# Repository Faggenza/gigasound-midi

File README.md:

# Gigasound MIDI Polyphonic Keyboard

A USB-connected MPE MIDI keyboard using piezoresistive sensors for expressive, pressure-sensitive input, built around the STM32F401 microcontroller.

## Source Tree

```
├── sprite/     # Assets in aseprite format
├── assets_src/ # Assets in bitmap format 
├── convert_asset.py # Asset convertion tool
├── emulator/
│   ├── emulator.h
│   └── Makefile
├── gigasound-hw/ # PCB KiCad files
├── include/
│   ├── adc.h
│   ├── assets.h
│   ├── bootloader.h
│   ├── calibrate.h
│   ├── config.h
│   ├── eeprom.h
│   ├── init.h
│   ├── input.h
│   ├── led.h
│   ├── main.h
│   ├── midi.h
│   ├── scale.h
│   ├── ssd1306.h
│   ├── stm32f4xx_it.h
│   ├── tusb_config.h
│   ├── uart.h
│   └── ui/
├── lib
│   └── gigagl # embedded graphics library
├── platformio.ini 
└── src/
    ├── adc.c
    ├── assets
    ├── calibrate.c
    ├── config.c
    ├── eeprom.c
    ├── init.c
    ├── input.c
    ├── led.c
    ├── main.c
    ├── midi.c
    ├── scale.c
    ├── stm32f4xx_hal_msp.c
    ├── stm32f4xx_it.c
    ├── uart.c
    ├── ui/               
    └── usb_descriptors.c
```

## References

MCU: [STM32F0401RE](https://www.st.com/resource/en/datasheet/stm32f401re.pdf)

Nucleo: [Schematic](https://www.st.com/resource/en/schematic_pack/mb1136-default-c04_schematic.pdf)

Piezoresistive sensor: [datasheet](https://cdn2.hubspot.net/hubfs/3899023/Interlinkelectronics%20November2017/Docs/Datasheet_FSR.pdf)

MIDI: [docs](https://drive.google.com/file/d/1QGjiK2QPPbii8YmES3vDEZlP63OGLiKr/view)

## Testing

[MPE Monitor](https://studiocode.dev/mpe-monitor/)

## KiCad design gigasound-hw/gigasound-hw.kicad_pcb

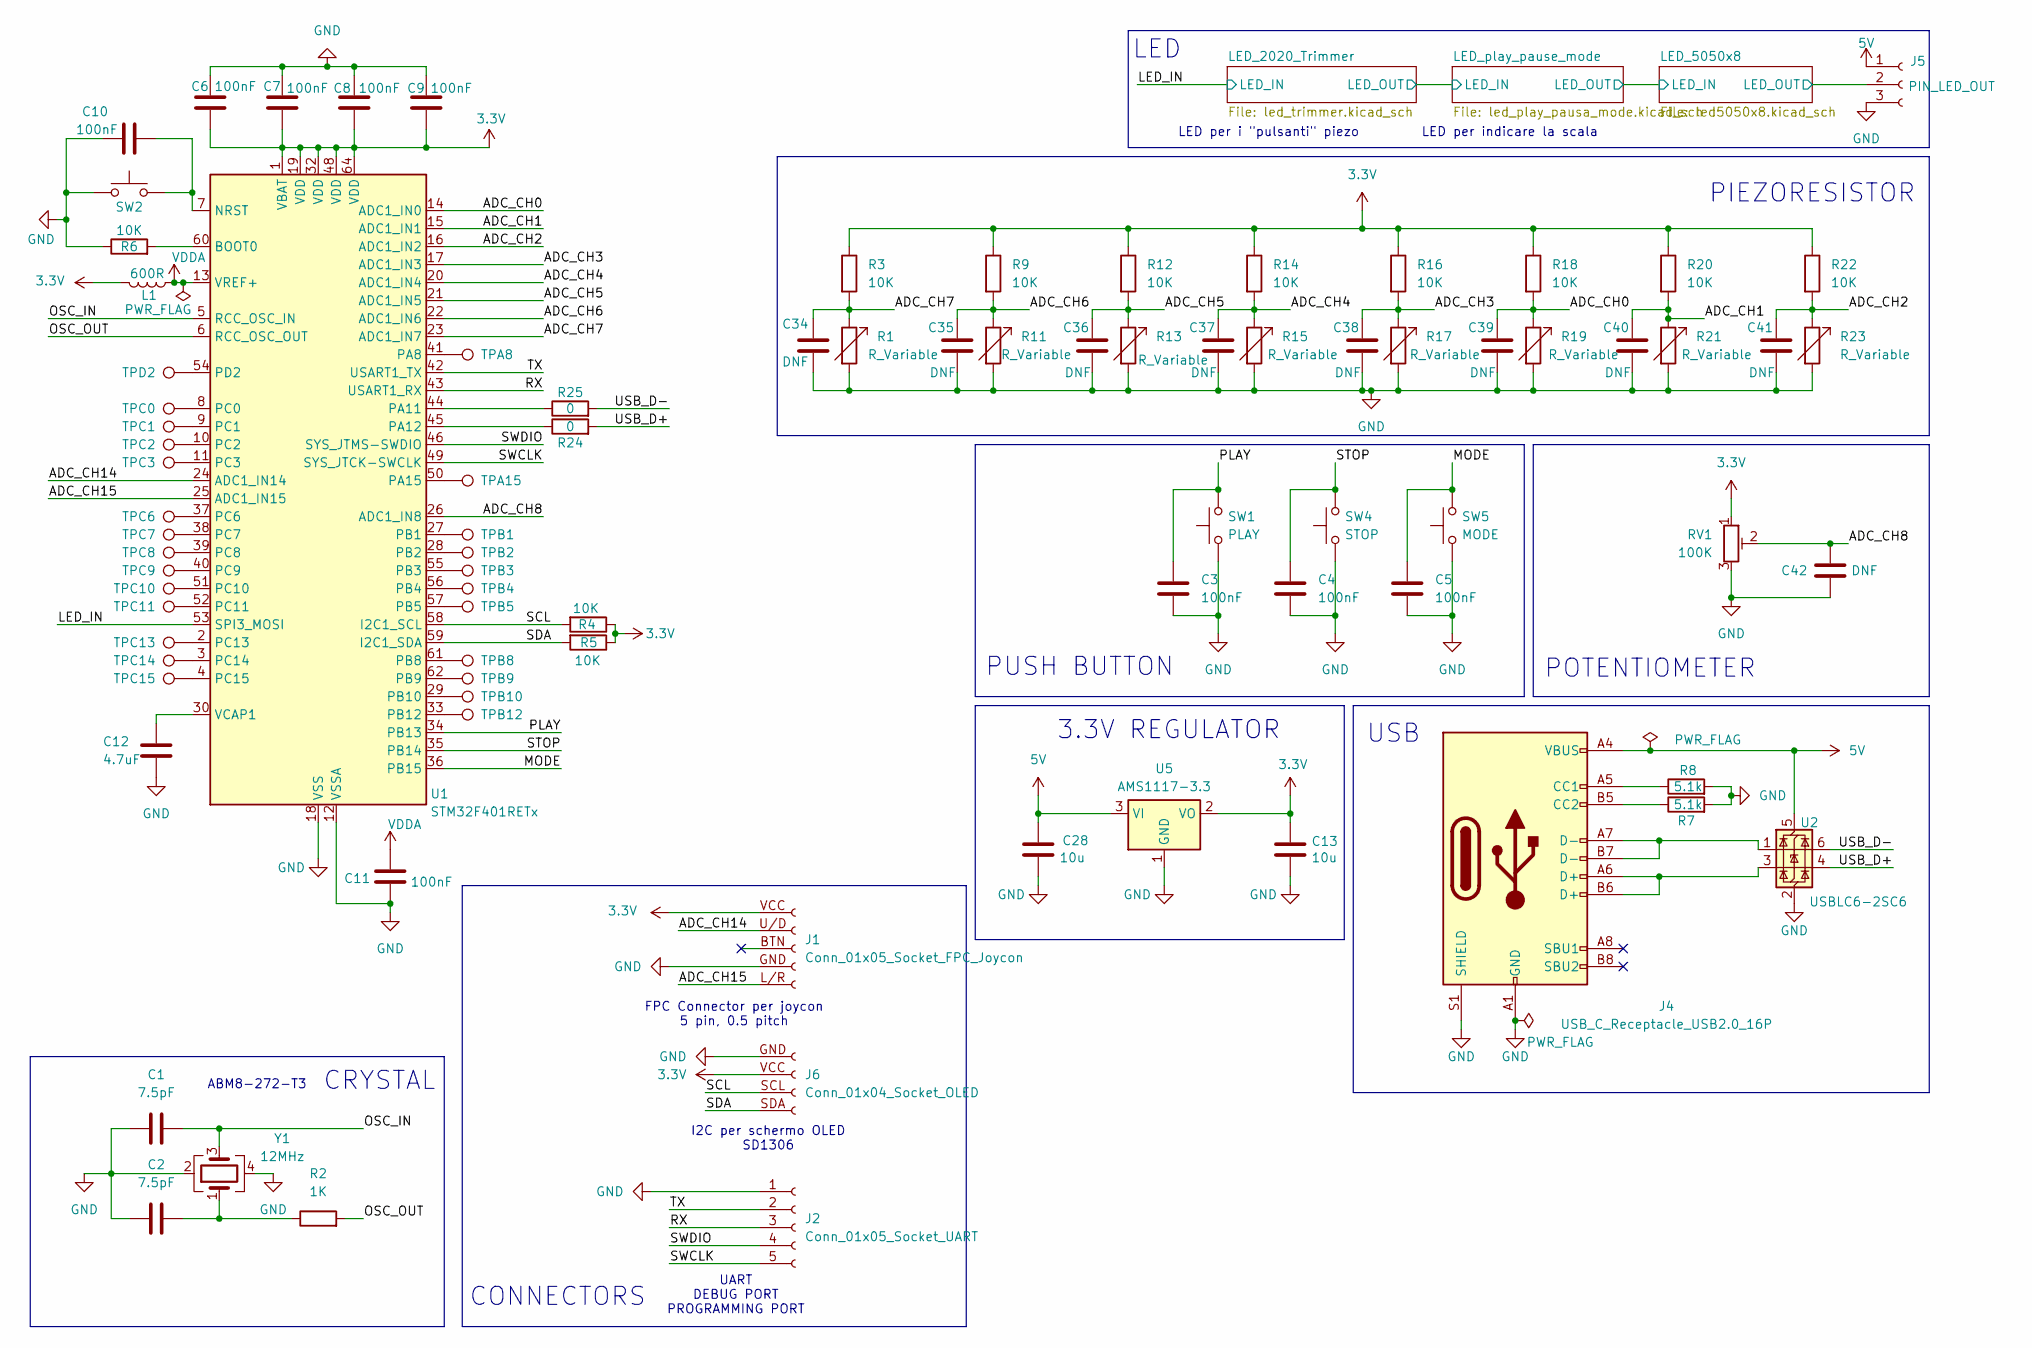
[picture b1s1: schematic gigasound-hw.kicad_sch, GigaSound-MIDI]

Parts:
C1, C2: 7.5pF; C_0402_1005Metric_Pad0.74x0.62mm_HandSolder
C3, C4, C5, C6, C7, C8, C9, C10, C11: 100nF; C_0402_1005Metric_Pad0.74x0.62mm_HandSolder
C12: 4.7uF; C_0805_2012Metric_Pad1.18x1.45mm_HandSolder
C13, C28: 10u; C_0805_2012Metric_Pad1.18x1.45mm_HandSolder
C34, C35, C36, C37, C38, C39, C40, C41, C42: DNF; C_0402_1005Metric_Pad0.74x0.62mm_HandSolder
J1: Conn_01x05_Socket_FPC_Joycon; Joycon-FPC-1x05-P0.5mm
J2: Conn_01x05_Socket_UART; PinHeader_1x05_P2.54mm_Vertical
J4: USB_C_Receptacle_USB2.0_16P; USB_C_Receptacle_G-Switch_GT-USB-7010ASV
J5: PIN_LED_OUT; PinHeader_1x03_P2.54mm_Vertical
J6: Conn_01x04_Socket_OLED; PinSocket_1x04_P2.54mm_Vertical_OLED_0.96inch
L1: 600R; L_0201_0603Metric_Pad0.64x0.40mm_HandSolder
R1, R11, R13, R15, R17, R19, R21, R23: R_Variable; FSR402
R2: 1K; R_0402_1005Metric_Pad0.72x0.64mm_HandSolder
R3, R4, R5, R6, R9, R12, R14, R16, R18, R20, R22: 10K; R_0402_1005Metric_Pad0.72x0.64mm_HandSolder
R7, R8: 5.1k; R_0402_1005Metric_Pad0.72x0.64mm_HandSolder
R24, R25: 0; R_0402_1005Metric_Pad0.72x0.64mm_HandSolder
RV1: 100K; Potentiometer_Alps_RK09K_Single_Vertical
SW1: PLAY; SW_SPST_TL3342
SW2: Reset; SW_Push_SPST_NO_Alps_SKRK
SW4: STOP; SW_SPST_TL3342
SW5: MODE; SW_SPST_TL3342
TPA8, TPA15: TestPoint_Pad_D1.0mm
TPB1, TPB2, TPB3, TPB4, TPB5, TPB8, TPB9, TPB10, TPB12: TestPoint_Pad_D1.0mm
TPC0, TPC1, TPC2, TPC3, TPC6, TPC7, TPC8, TPC9, TPC10, TPC11, TPC13, TPC14, TPC15: TestPoint_Pad_D1.0mm
TPD2: TestPoint_Pad_D1.0mm
U1: STM32F401RETx; LQFP-64_10x10mm_P0.5mm
U2: USBLC6-2SC6; SOT-23-6
U5: AMS1117-3.3; SOT-223-3_TabPin2
Y1: 12MHz; Crystal_SMD_3225-4Pin_3.2x2.5mm

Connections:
3.3V: C6.2, C7.2, C8.2, C9.2, C13.1, J1.VCC, J6.VCC, L1.2, R3.1, R4.1, R5.1, R9.1, R12.1, R14.1, R16.1, R18.1, R20.1, R22.1, RV1.1, U1.1 (VBAT), U1.19 (VDD), U1.32 (VDD), U1.48 (VDD), U1.64 (VDD), U5.2 (VO)
5V: C28.1, J4.A4 (VBUS), J4.A9 (VBUS), J4.B4 (VBUS), J4.B9 (VBUS), J5.1, U2.5 (VBUS), U5.3 (VI); also elsewhere on the board
/ADC_CH0: C34.2, R1.1, R3.2, U1.23 (ADC1_IN7)
/ADC_CH1: C35.2, R9.2, R11.1, U1.22 (ADC1_IN6)
/ADC_CH2: C36.2, R12.2, R13.1, U1.21 (ADC1_IN5)
/ADC_CH3: C37.2, R14.2, R15.1, U1.20 (ADC1_IN4)
/ADC_CH4: C38.2, R16.2, R17.1, U1.17 (ADC1_IN3)
/ADC_CH5: C39.2, R18.2, R19.1, U1.14 (ADC1_IN0)
/ADC_CH6: C40.2, R20.2, R21.1, U1.15 (ADC1_IN1)
/ADC_CH7: C41.2, R22.2, R23.1, U1.16 (ADC1_IN2)
/ADC_CH8: C42.2, RV1.2, U1.26 (ADC1_IN8)
/ADC_CH14: J1.U/D, U1.24 (ADC1_IN14)
/ADC_CH15: J1.L/R, U1.25 (ADC1_IN15)
/LED_5050x8/LED_OUT: J5.2; also elsewhere on the board
/LED_IN: U1.53 (SPI3_MOSI); also elsewhere on the board
/MODE: C5.1, SW5.2, U1.36 (PB15)
/OSC_IN: C1.2, U1.5 (RCC_OSC_IN), Y1.3
/OSC_OUT: R2.2, U1.6 (RCC_OSC_OUT)
/PLAY: C3.1, SW1.2, U1.34 (PB13)
/RX: J2.3 (RX), U1.43 (USART1_RX)
/SCL: J6.SCL, R5.2, U1.58 (I2C1_SCL)
/SDA: J6.SDA, R4.2, U1.59 (I2C1_SDA)
/STOP: C4.1, SW4.2, U1.35 (PB14)
/SWCLK: J2.5 (SWCLK), U1.49 (SYS_JTCK-SWCLK)
/SWDIO: J2.4 (SWDIO), U1.46 (SYS_JTMS-SWDIO)
/TX: J2.2 (TX), U1.42 (USART1_TX)
/USB_D+: R24.2, U2.4 (I/O2)
/USB_D-: R25.2, U2.6 (I/O1)
GND: C1.1, C2.1, C3.2, C4.2, C5.2, C6.1, C7.1, C8.1, C9.1, C10.1, C11.2, C12.1, C13.2, C28.2, C34.1, C35.1, C36.1, C37.1, C38.1, C39.1, C40.1, C41.1, C42.1, J1.GND, J2.1 (GND), J4.A1 (GND), J4.A12 (GND), J4.B1 (GND), J4.B12 (GND), J4.S1 (SHIELD), J5.3, J6.GND, R1.2, R6.1, R7.2, R8.2, R11.2, R13.2, R15.2, R17.2, R19.2, R21.2, R23.2, RV1.3, SW1.1, SW2.1, SW4.1, SW5.1, U1.12 (VSSA), U1.18 (VSS), U1.31 (VSS), U1.47 (VSS), U1.63 (VSS), U2.2 (GND), U5.1 (GND), Y1.2, Y1.4; also elsewhere on the board
unnamed: C2.2, R2.1, Y1.1
unnamed: J4.A5 (CC1), R8.1
unnamed: J4.B5 (CC2), R7.1
unnamed: J4.A6 (D+), J4.B6 (D+), U2.3 (I/O2)
unnamed: J4.A7 (D-), J4.B7 (D-), U2.1 (I/O1)
unnamed: R6.2, U1.60 (BOOT0)
unnamed: C10.2, SW2.2, U1.7 (NRST)
unnamed: TPA8.1, U1.41 (PA8)
unnamed: R25.1, U1.44 (PA11)
unnamed: R24.1, U1.45 (PA12)
unnamed: TPA15.1, U1.50 (PA15)
unnamed: TPB1.1, U1.27 (PB1)
unnamed: TPB2.1, U1.28 (PB2)
unnamed: TPB3.1, U1.55 (PB3)
unnamed: TPB4.1, U1.56 (PB4)
unnamed: TPB5.1, U1.57 (PB5)
unnamed: TPB8.1, U1.61 (PB8)
unnamed: TPB9.1, U1.62 (PB9)
unnamed: TPB10.1, U1.29 (PB10)
unnamed: TPB12.1, U1.33 (PB12)
unnamed: TPC0.1, U1.8 (PC0)
unnamed: TPC1.1, U1.9 (PC1)
unnamed: TPC2.1, U1.10 (PC2)
unnamed: TPC3.1, U1.11 (PC3)
unnamed: TPC6.1, U1.37 (PC6)
unnamed: TPC7.1, U1.38 (PC7)
unnamed: TPC8.1, U1.39 (PC8)
unnamed: TPC9.1, U1.40 (PC9)
unnamed: TPC10.1, U1.51 (PC10)
unnamed: TPC11.1, U1.52 (PC11)
unnamed: TPC13.1, U1.2 (PC13)
unnamed: TPC14.1, U1.3 (PC14)
unnamed: TPC15.1, U1.4 (PC15)
unnamed: TPD2.1, U1.54 (PD2)
unnamed: C12.2, U1.30 (VCAP1)
VDDA: C11.1, L1.1, U1.13 (VREF+)

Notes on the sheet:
LED per i "pulsanti" piezo
USB
FPC Connector per joycon 5 pin, 0.5 pitch
POTENTIOMETER
CONNECTORS
3.3V REGULATOR
I2C per schermo OLED SD1306
LED per indicare la scala
PIEZORESISTOR
LED
UART DEBUG PORT PROGRAMMING PORT
ABM8-272-T3
PUSH BUTTON
CRYSTAL

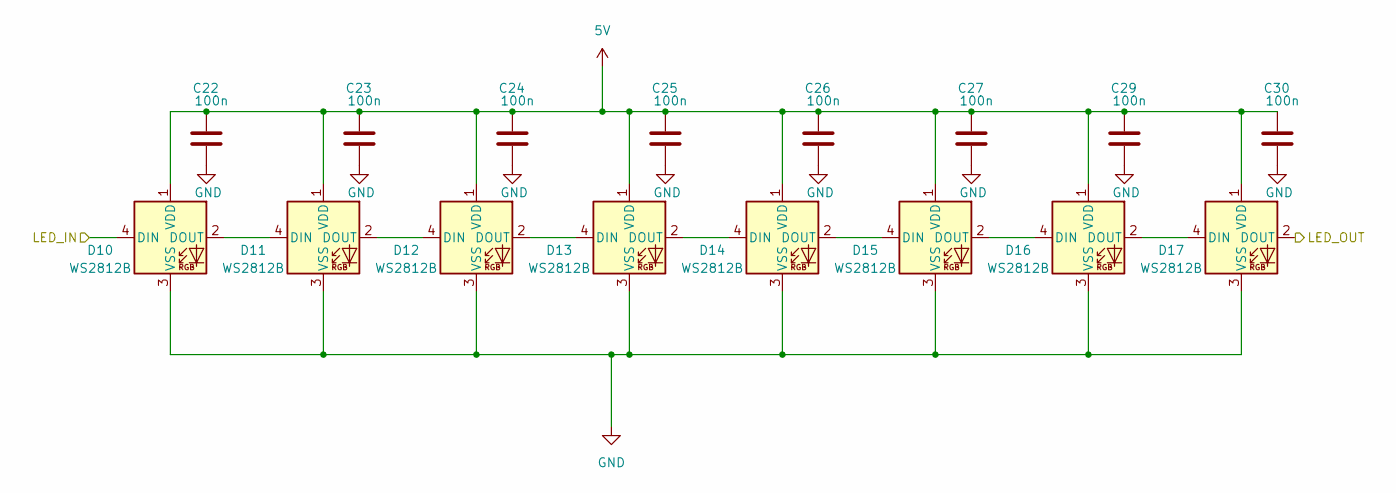
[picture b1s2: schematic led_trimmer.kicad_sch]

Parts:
C22, C23, C24, C25, C26, C27, C29, C30: 100n; C_0402_1005Metric_Pad0.74x0.62mm_HandSolder
D10, D11, D12, D13, D14, D15, D16, D17: WS2812B; LED_WS2812B-2020_PLCC4_2.0x2.0mm

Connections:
5V: C22.1, C23.1, C24.1, C25.1, C26.1, C27.1, C29.1, C30.1, D10.1 (VDD), D11.1 (VDD), D12.1 (VDD), D13.1 (VDD), D14.1 (VDD), D15.1 (VDD), D16.1 (VDD), D17.1 (VDD); also elsewhere on the board
/LED_2020_Trimmer/LED_OUT: D17.2 (DOUT); also elsewhere on the board
/LED_IN: D10.4 (DIN); also elsewhere on the board
GND: C22.2, C23.2, C24.2, C25.2, C26.2, C27.2, C29.2, C30.2, D10.3 (VSS), D11.3 (VSS), D12.3 (VSS), D13.3 (VSS), D14.3 (VSS), D15.3 (VSS), D16.3 (VSS), D17.3 (VSS); also elsewhere on the board
unnamed: D10.2 (DOUT), D11.4 (DIN)
unnamed: D11.2 (DOUT), D12.4 (DIN)
unnamed: D12.2 (DOUT), D13.4 (DIN)
unnamed: D13.2 (DOUT), D14.4 (DIN)
unnamed: D14.2 (DOUT), D15.4 (DIN)
unnamed: D15.2 (DOUT), D16.4 (DIN)
unnamed: D16.2 (DOUT), D17.4 (DIN)

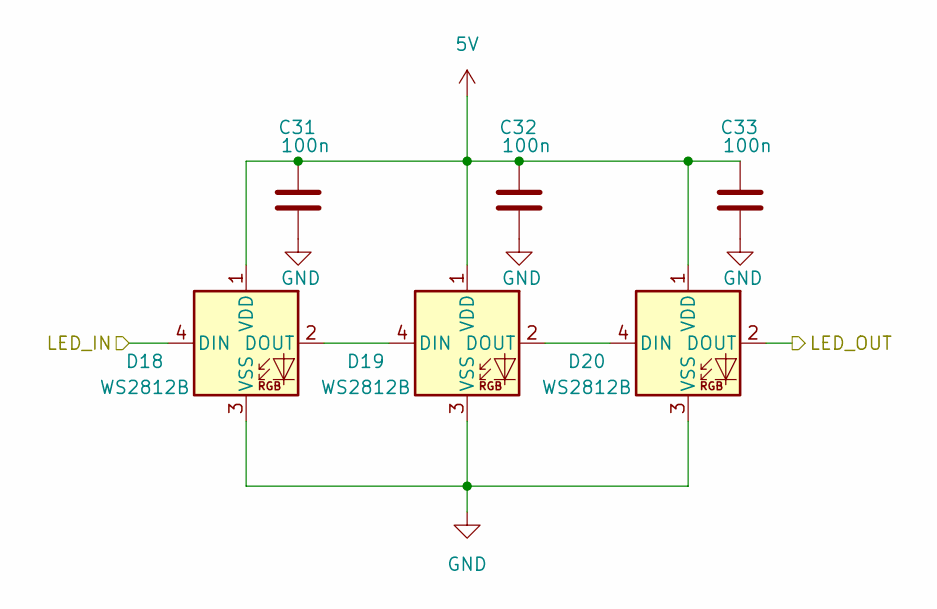
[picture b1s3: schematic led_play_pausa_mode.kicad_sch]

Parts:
C31, C32, C33: 100n; C_0402_1005Metric_Pad0.74x0.62mm_HandSolder
D18, D19, D20: WS2812B; LED_WS2812B-2020_PLCC4_2.0x2.0mm

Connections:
5V: C31.1, C32.1, C33.1, D18.1 (VDD), D19.1 (VDD), D20.1 (VDD); also elsewhere on the board
/LED_2020_Trimmer/LED_OUT: D18.4 (DIN); also elsewhere on the board
/LED_5050x8/LED_IN: D20.2 (DOUT); also elsewhere on the board
GND: C31.2, C32.2, C33.2, D18.3 (VSS), D19.3 (VSS), D20.3 (VSS); also elsewhere on the board
unnamed: D18.2 (DOUT), D19.4 (DIN)
unnamed: D19.2 (DOUT), D20.4 (DIN)

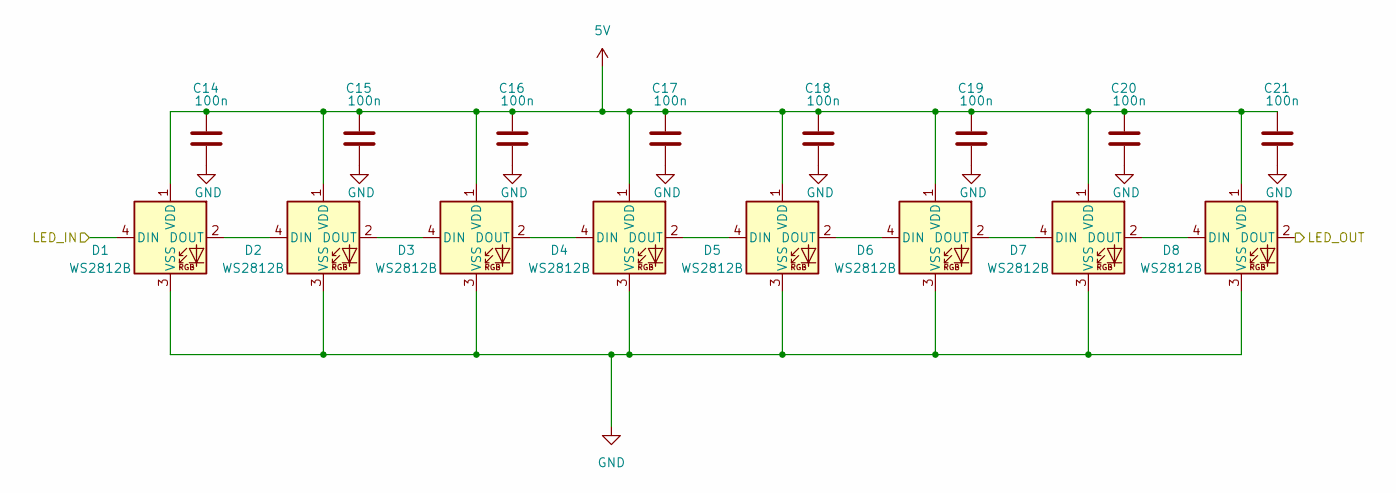
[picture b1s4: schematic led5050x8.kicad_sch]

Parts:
C14, C15, C16, C17, C18, C19, C20, C21: 100n; C_0402_1005Metric_Pad0.74x0.62mm_HandSolder
D1, D2, D3, D4, D5, D6, D7, D8: WS2812B; LED_WS2812B_PLCC4_5.0x5.0mm_P3.2mm

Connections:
5V: C14.1, C15.1, C16.1, C17.1, C18.1, C19.1, C20.1, C21.1, D1.1 (VDD), D2.1 (VDD), D3.1 (VDD), D4.1 (VDD), D5.1 (VDD), D6.1 (VDD), D7.1 (VDD), D8.1 (VDD); also elsewhere on the board
/LED_5050x8/LED_IN: D1.4 (DIN); also elsewhere on the board
/LED_5050x8/LED_OUT: D8.2 (DOUT); also elsewhere on the board
GND: C14.2, C15.2, C16.2, C17.2, C18.2, C19.2, C20.2, C21.2, D1.3 (VSS), D2.3 (VSS), D3.3 (VSS), D4.3 (VSS), D5.3 (VSS), D6.3 (VSS), D7.3 (VSS), D8.3 (VSS); also elsewhere on the board
unnamed: D1.2 (DOUT), D2.4 (DIN)
unnamed: D2.2 (DOUT), D3.4 (DIN)
unnamed: D3.2 (DOUT), D4.4 (DIN)
unnamed: D4.2 (DOUT), D5.4 (DIN)
unnamed: D5.2 (DOUT), D6.4 (DIN)
unnamed: D6.2 (DOUT), D7.4 (DIN)
unnamed: D7.2 (DOUT), D8.4 (DIN)

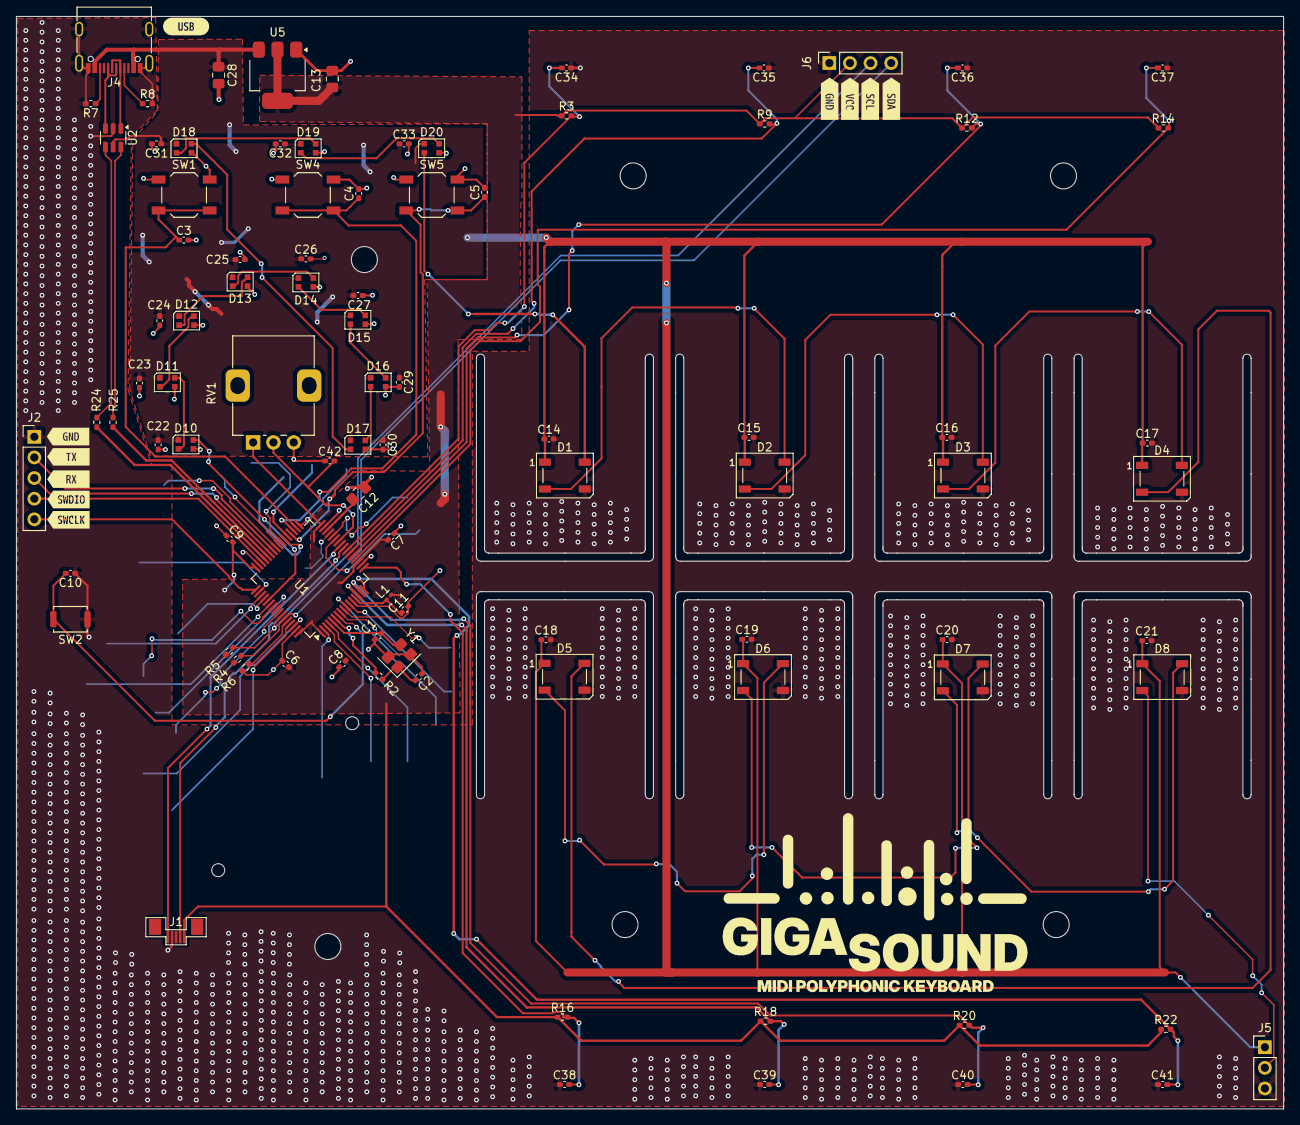
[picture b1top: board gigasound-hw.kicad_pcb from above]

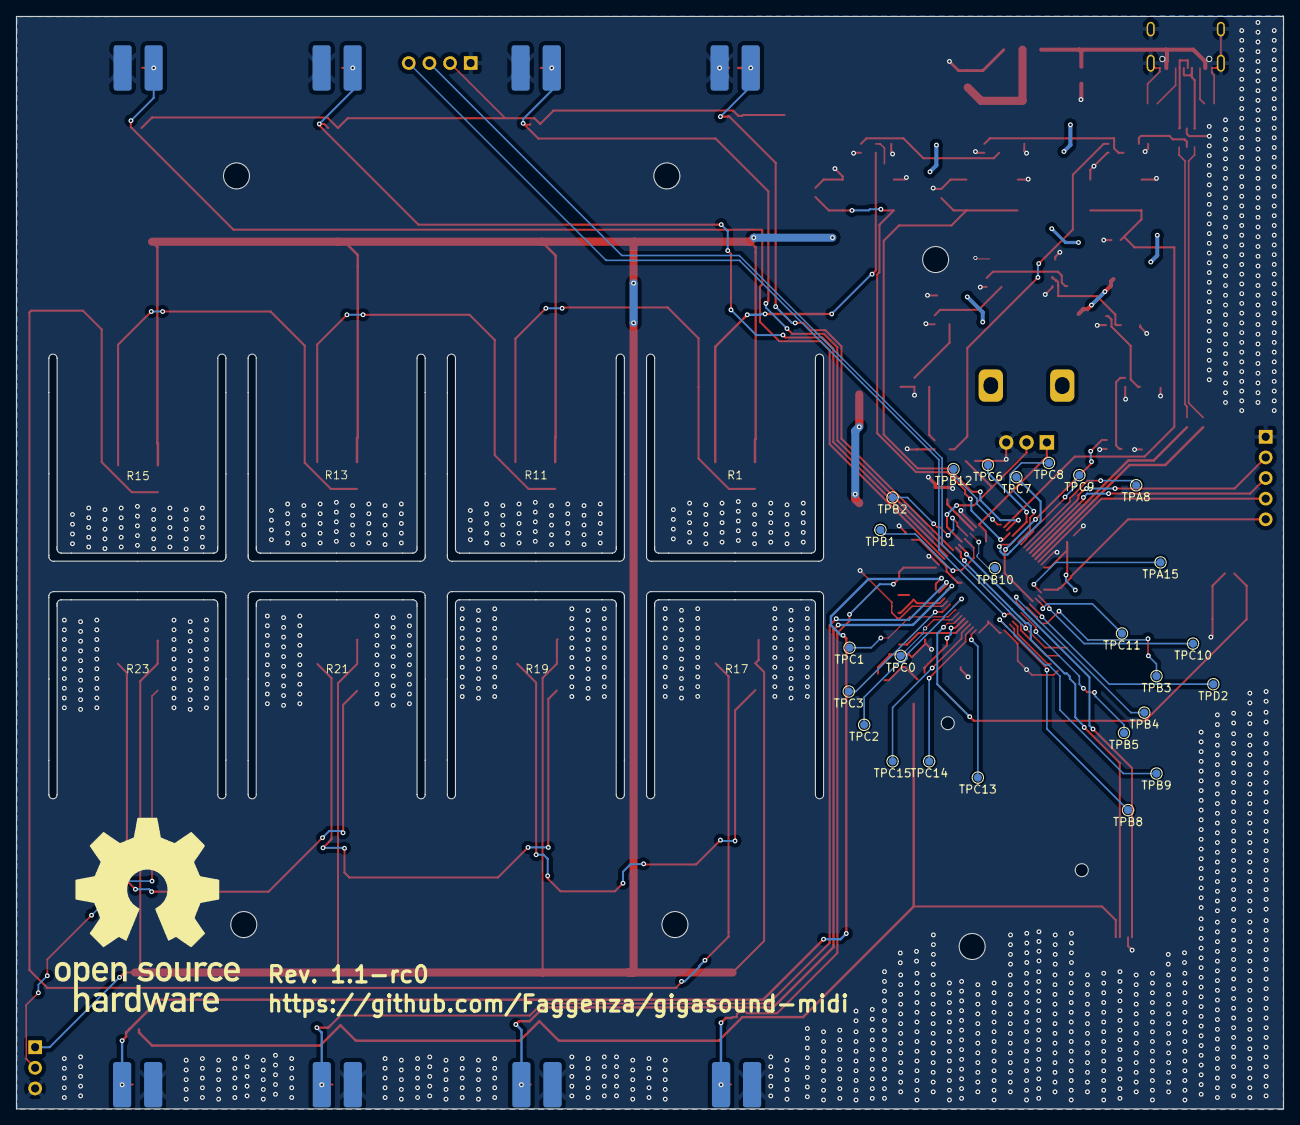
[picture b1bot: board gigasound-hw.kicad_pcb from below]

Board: 2 copper layers, 156.1 x 134.5 mm, 135 parts (33 on the bottom side), 83 nets.

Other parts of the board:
kibuzzard-682F341C, kibuzzard-682F341C#2: G***; kibuzzard-682F341C
kibuzzard-682F343C: G***; kibuzzard-682F343C
kibuzzard-682F3431: G***; kibuzzard-682F3431
kibuzzard-682F3436: G***; kibuzzard-682F3436
kibuzzard-682F3442: G***; kibuzzard-682F3442
kibuzzard-682F3456: G***; kibuzzard-682F3456
kibuzzard-68303C3B: G***; kibuzzard-68303C3B
kibuzzard-68303C17: G***; kibuzzard-68303C17
kibuzzard-68303C33: G***; kibuzzard-68303C33

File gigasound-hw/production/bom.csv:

Designator,Footprint,Quantity,Value,LCSC Part #
"C1, C2",0402,2,7.5pF,
"C10, C11, C3, C4, C5, C6, C7, C8, C9",0402,9,100nF,
C12,0805,1,4.7uF,
"C13, C28",0805,2,10u,
"C14, C15, C16, C17, C18, C19, C20, C21, C22, C23, C24, C25, C26, C27, C29, C30, C31, C32, C33",0402,19,100n,
"C34, C35, C36, C37, C38, C39, C40, C41, C42",0402,9,DNF,
"D1, D2, D3, D4, D5, D6, D7, D8",LED_WS2812B_PLCC4_5.0x5.0mm_P3.2mm,8,WS2812B,
"D10, D11, D12, D13, D14, D15, D16, D17, D18, D19, D20",LED_WS2812B-2020_PLCC4_2.0x2.0mm,11,WS2812B,
J1,Joycon-FPC-1x05-P0.5mm,1,Conn_01x05_Socket_FPC_Joycon,
J2,PinHeader_1x05_P2.54mm_Vertical,1,Conn_01x05_Socket_UART,
J4,USB_C_Receptacle_G-Switch_GT-USB-7010ASV,1,USB_C_Receptacle_USB2.0_16P,
J5,PinHeader_1x01_P1.00mm_Vertical,1,PIN_LED_OUT,
J6,PinSocket_1x04_P2.54mm_Vertical_OLED_0.96inch,1,Conn_01x04_Socket_OLED,
L1,0201,1,600R,
"R1, R11, R13, R15, R17, R19, R21, R23",FSR402,8,R_Variable,
"R12, R14, R16, R18, R20, R22, R3, R4, R5, R6, R9",0402,11,10K,
R2,0402,1,1K,
"R24, R25",0402,2,0,
"R7, R8",0402,2,5.1k,
RV1,Potentiometer_Alps_RK09K_Single_Vertical,1,100K,
SW1,SW_SPST_TL3342,1,PLAY,
SW2,SW_Push_SPST_NO_Alps_SKRK,1,Reset,
SW4,SW_SPST_TL3342,1,STOP,
SW5,SW_SPST_TL3342,1,MODE,
"TPA15, TPA8, TPB1, TPB10, TPB12, TPB2, TPB3, TPB4, TPB5, TPB8, TPB9, TPC0, TPC1, TPC10, TPC11, TPC13, TPC14, TPC15, TPC2, TPC3, TPC6, TPC7, TPC8, TPC9, TPD2",TestPoint_Pad_D1.0mm,25,~,
U1,LQFP-64_10x10mm_P0.5mm,1,STM32F401RETx,
U2,SOT-23-6,1,USBLC6-2SC6,
U5,SOT-223-3_TabPin2,1,AMS1117-3.3,
Y1,Crystal_SMD_3225-4Pin_3.2x2.5mm,1,12MHz,

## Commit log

2025-04-30 init
2025-04-30 example
2025-04-30 debug
2025-04-30 try uart
2025-05-07 compile with latest gcc
2025-05-07 fix uart
2025-05-07 add some symbols
2025-05-07 progress hw schematic
2025-05-07 Fix adc
2025-05-07 hw: added usb, 3.3v, cleaned up
2025-05-14 readme
2025-05-14 working ws2812
2025-05-14 add led to sch
2025-05-14 ws2812 driver
2025-05-14 add led dma control
2025-05-14 add adc dma support
2025-05-14 implement dma adc
2025-05-14 fix GIGA error
2025-05-15 add submodule and clock config
2025-05-15 msp usb
2025-05-15 add tinyusb midi example
2025-05-15 added tinyusb example midi
2025-05-15 add footprint
2025-05-20 Fix midi
2025-05-20 hw: footprints
2025-05-20 hw: initial placement
2025-05-21 hw: Finished footprints
2025-05-21 hw: finish layout
2025-05-21 hw: start routing
2025-05-21 hw: finish routing
2025-05-21 hw: add GND plane
2025-05-22 hw: added esd protection and caps
2025-05-22 hw: silkscreen
2025-05-22 hw: fix drc errors
2025-05-22 hw: gigasound logo
2025-05-23 hw: add mounting holes
2025-05-23 hw: fix vias on silkscreen
2025-05-23 hw: final touches
2025-05-28 remove production files
2025-05-28 fw: MPE midi commands
2025-05-28 fw: Cafe'
2025-05-28 ui: some sprites
2025-06-17 fix clock
2025-06-17 hw: fix big mistake
2025-06-17 fw: fix HSE clock
2025-06-17 fw: dfu and oled
2025-06-18 fw: working display without dma
2025-06-18 fw: Buttons
2025-06-18 fw: fix dma oled
2025-06-18 fw: rotate screen
2025-06-18 fw: deinit gpio
2025-06-18 add gigagl
2025-06-18 fw: fix oled direction
2025-06-18 fw: reimport gigagl
2025-06-18 fw: fix gigagl
2025-06-18 fw: delete old tinyusb library
2025-06-18 fw: fix gigagl import
2025-06-18 fw: joycon calibration
2025-06-18 fw: fix animations
2025-06-19 fw: fix menu animation
2025-06-19 hw: new pcb revision candidate
2025-06-19 fw: fix adc order
2025-06-19 fw: modularize adc and input
2025-06-19 fw: insert font
2025-06-19 fw: FONT
2025-06-19 fw: compiler is too powerful
2025-06-19 font adjustment
2025-06-19 font shift 1 row
2025-06-19 schifo
2025-06-19 fw: fix uppercase fonts
2025-06-19 font
2025-06-19 font: make 'i' slimmer
2025-06-26 fw: start state machine
2025-06-26 fw: fix asset importing
2025-06-27 fw: all buttons
2025-06-27 fw: start led custom
2025-06-27 fw: add eeprom emulation
2025-06-27 fw: led color screen
2025-06-28 fw: clean imports and implement simple emulator
2025-06-28 fw: custom leds
2025-06-28 fw: add animations and refactor main
2025-06-28 fw: misc
2025-06-28 fw: beautiful back animation
2025-06-28 add home asset
2025-06-29 fw: implemented scales
2025-06-29 assets: start keyboard from do
2025-06-29 fw: refactor list animations
2025-06-29 fw: implemented font
2025-06-29 fw: add scale selection
2025-06-30 fw: add key feedback
2025-06-30 fw: small input tweaks
2025-06-30 fw: squash final bugs
2025-06-30 fw: fix led screen
2025-06-30 fw: small fix
2025-06-30 fw: fix notes off when changed
2025-07-03 fw: missing state change
2025-07-11 add readme and remove old files
2025-07-12 Implemented joycon button
2025-07-12 fw: fix all warnings
2025-07-13 fw: improve button debounce
2025-07-13 fw: fix pressure > 127
2025-07-13 fw: fix do diesis
2025-07-13 fw: implement knob hysteresis
2025-07-13 fw: add adc debug screen
2025-07-13 fw: implemented velocity
2025-07-13 fw: fix clearing leds on change
2025-07-13 fw: led screen animation
